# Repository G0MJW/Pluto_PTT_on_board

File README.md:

# Pluto_PTT_on_board
PCB for PTT out by F5OEO
Requires updated firmware from F5OEO

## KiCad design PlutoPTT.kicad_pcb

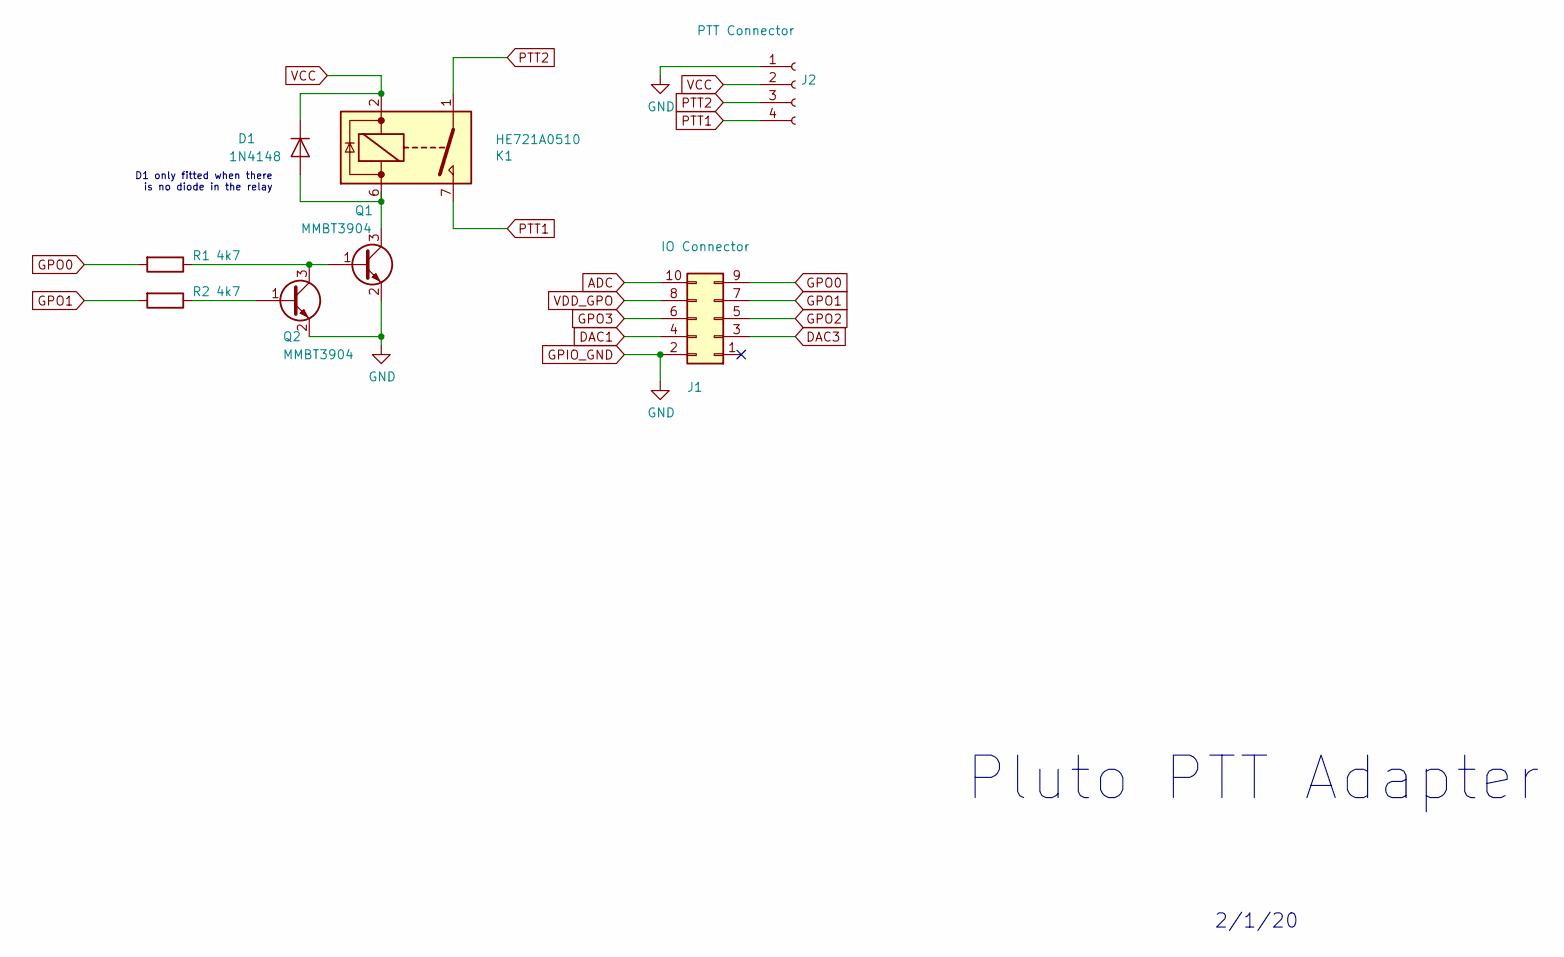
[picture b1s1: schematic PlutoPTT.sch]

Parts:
D1: 1N4148; D_1206_3216Metric
J1: IO Connector; PinHeader_2x05_P2.54mm_Vertical
J2: PTT Connector; PinHeader_1x04_P2.54mm_Horizontal
K1: HE721A0510; Relay_StandexMeder_DIP_LowProfile
Q1, Q2: MMBT3904; SOT-23
R1, R2: 4k7; R_0805_2012Metric_Pad1.15x1.40mm_HandSolder

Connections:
ADC: J1.10
DAC1: J1.4
DAC3: J1.3
GPIO_GND: J1.2, J2.1, Q1.2 (E), Q2.2 (E)
GPO0: J1.9, R1.2
GPO1: J1.7, R2.2
GPO2: J1.5
GPO3: J1.6
unnamed: D1.2 (A), K1.6, Q1.3 (C)
unnamed: Q1.1 (B), Q2.3 (C), R1.1
unnamed: Q2.1 (B), R2.1
PTT1: J2.4, K1.7, K1.8
PTT2: J2.3, K1.1, K1.14
VCC: D1.1 (K), J2.2, K1.2, K1.13
VDD_GPO: J1.8

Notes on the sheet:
Pluto PTT Adapter
2/1/20
D1 only fitted when there is no diode in the relay

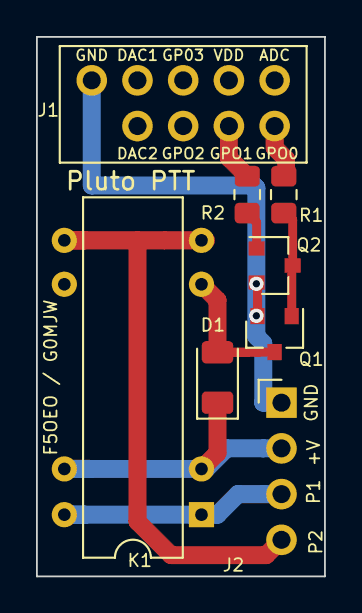
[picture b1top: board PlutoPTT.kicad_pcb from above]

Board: 2 copper layers, 16.0 x 30.0 mm, 8 parts (0 on the bottom side), 9 nets.

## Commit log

2020-01-05 Deleting old gerbers
